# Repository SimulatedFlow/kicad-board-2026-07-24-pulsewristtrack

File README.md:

# 2026-07-24-pulsewristtrack

<!-- SF-STORE-BLOCK:BEGIN -->
## 🛒 Source-available — see before you buy

This repository contains the **full design files** of a commercial hardware board. It is **source-available, not open source**: read it, evaluate it, then buy a license to use it. See **LICENSE.md (source-available, purchase required)**.

**Get it / Buy:**
- **Order on eBay** (this board, bare PCB): https://www.ebay.de/itm/398223633551
- Product page (specs, photos, price): https://simulatedflow.teufel-engineering.com/platinen/2026-07-24-pulsewristtrack/
- eBay store — all our boards and PCB art: https://www.ebay.de/usr/simula-9
- Merch shop (dev & gaming): https://simulatedflow.myspreadshop.de
- Merch shop (Synthetica / EDM): https://synthetica.myspreadshop.de
- Direct / invoice (Simulated Flow UG): simulatedflow@gmail.com

### 📬 **Free Board Documentation & Firmware Pack**

Schematics, BOMs and example-firmware docs for our STM32 carrier boards. Get it by joining the newsletter — plus a heads-up when something new ships. Double opt-in, unsubscribe in one click, no address sharing.

👉 **[Get the free pack](https://simulatedflow.teufel-engineering.com/newsletter/hardware/?q=gh)**

_© 2026 Simulated Flow UG. All rights reserved._
<!-- SF-STORE-BLOCK:END -->

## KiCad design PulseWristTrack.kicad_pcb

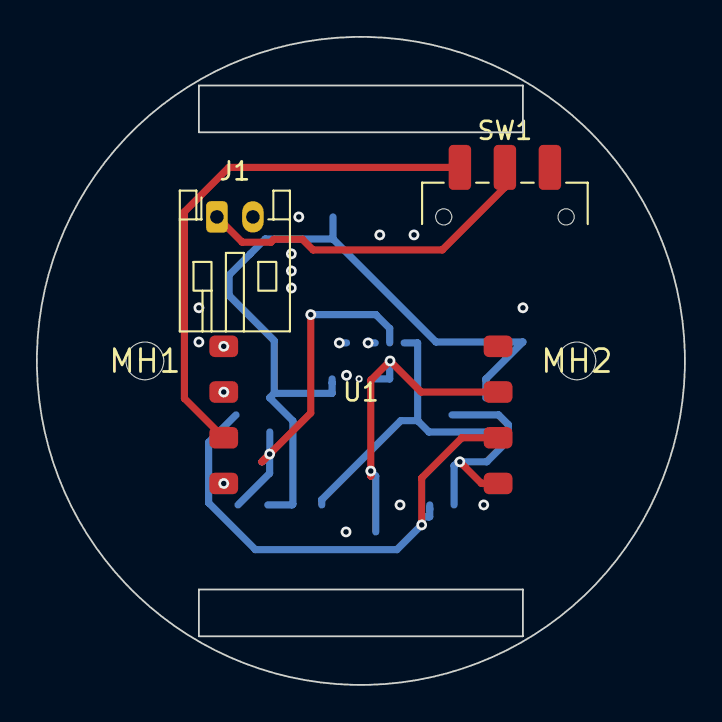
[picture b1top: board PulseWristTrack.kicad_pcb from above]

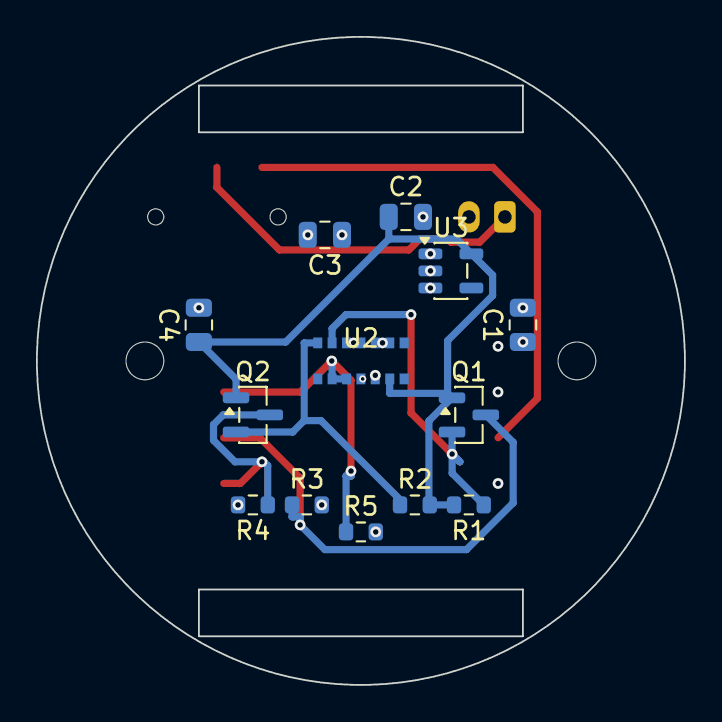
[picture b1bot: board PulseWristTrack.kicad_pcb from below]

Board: 4 copper layers, 36.0 x 36.0 mm, 18 parts (13 on the bottom side), 10 nets.

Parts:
C1, C3: 10uF; C_0805_2012Metric
C2, C4: 1uF; C_0805_2012Metric
J1: BATT_JST_PH; JST_PH_S2B-PH-K_1x02_P2.00mm_Horizontal
MH1, MH2: MountingHole_2.1mm
Q1, Q2: BSS138; SOT-23
R1, R2, R3, R4: 4.7k; R_0603_1608Metric
R5: 10k; R_0603_1608Metric
SW1: JS102011SAQN; SW_SPDT_CK_JS102011SAQN
U1: XIAO_nRF52840_Sense; XIAO_nRF52840
U2: MAX30102; MAX30102_OLGA14
U3: AP2112K-1.8; SOT-23-5

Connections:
+1V8: C2.1, C4.1, Q1.1, Q2.1, R1.2, R2.2, U2.9, U3.5
+3V3: C1.1, C3.1, R3.2, R4.2, R5.2, U1.3V3, U2.5, U2.6, U2.10, U3.1, U3.3
BAT+: J1.1, SW1.2
BAT_SW: SW1.1, U1.BAT+
GND: C1.2, C2.2, C3.2, C4.2, J1.2, U1.BAT-, U1.GND, U2.3, U2.4, U2.11, U3.2
INT: R5.1, U1.D3, U2.12, U2.13
SCL_1V8: Q2.2, R2.1, U2.1
SCL_3V3: Q2.3, R4.1, U1.D5
SDA_1V8: Q1.2, R1.1, U2.2
SDA_3V3: Q1.3, R3.1, U1.D4

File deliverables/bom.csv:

"Refs","Value","Footprint","Qty","DNP"
"C1","10uF","Capacitor_SMD:C_0805_2012Metric","1",""
"C2","1uF","Capacitor_SMD:C_0805_2012Metric","1",""
"C3","10uF","Capacitor_SMD:C_0805_2012Metric","1",""
"C4","1uF","Capacitor_SMD:C_0805_2012Metric","1",""
"J1","LiPo","Connector_JST:JST_PH_S2B-PH-K_1x02_P2.00mm_Horizontal","1",""
"Q1","BSS138","Package_TO_SOT_SMD:SOT-23","1",""
"Q2","BSS138","Package_TO_SOT_SMD:SOT-23","1",""
"R1","4.7k","Resistor_SMD:R_0603_1608Metric","1",""
"R2","4.7k","Resistor_SMD:R_0603_1608Metric","1",""
"R3","4.7k","Resistor_SMD:R_0603_1608Metric","1",""
"R4","4.7k","Resistor_SMD:R_0603_1608Metric","1",""
"R5","10k","Resistor_SMD:R_0603_1608Metric","1",""
"SW1","JS202011MQN","Button_Switch_SMD:SW_SPDT_PCM12","1",""
"U1","XIAO nRF52840 Sense","PulseWristTrack:XIAO_nRF52840","1",""
"U2","MAX30102","PulseWristTrack:MAX30102_OLGA14","1",""
"U3","AP2112K-1.8","Package_TO_SOT_SMD:SOT-23-5","1",""

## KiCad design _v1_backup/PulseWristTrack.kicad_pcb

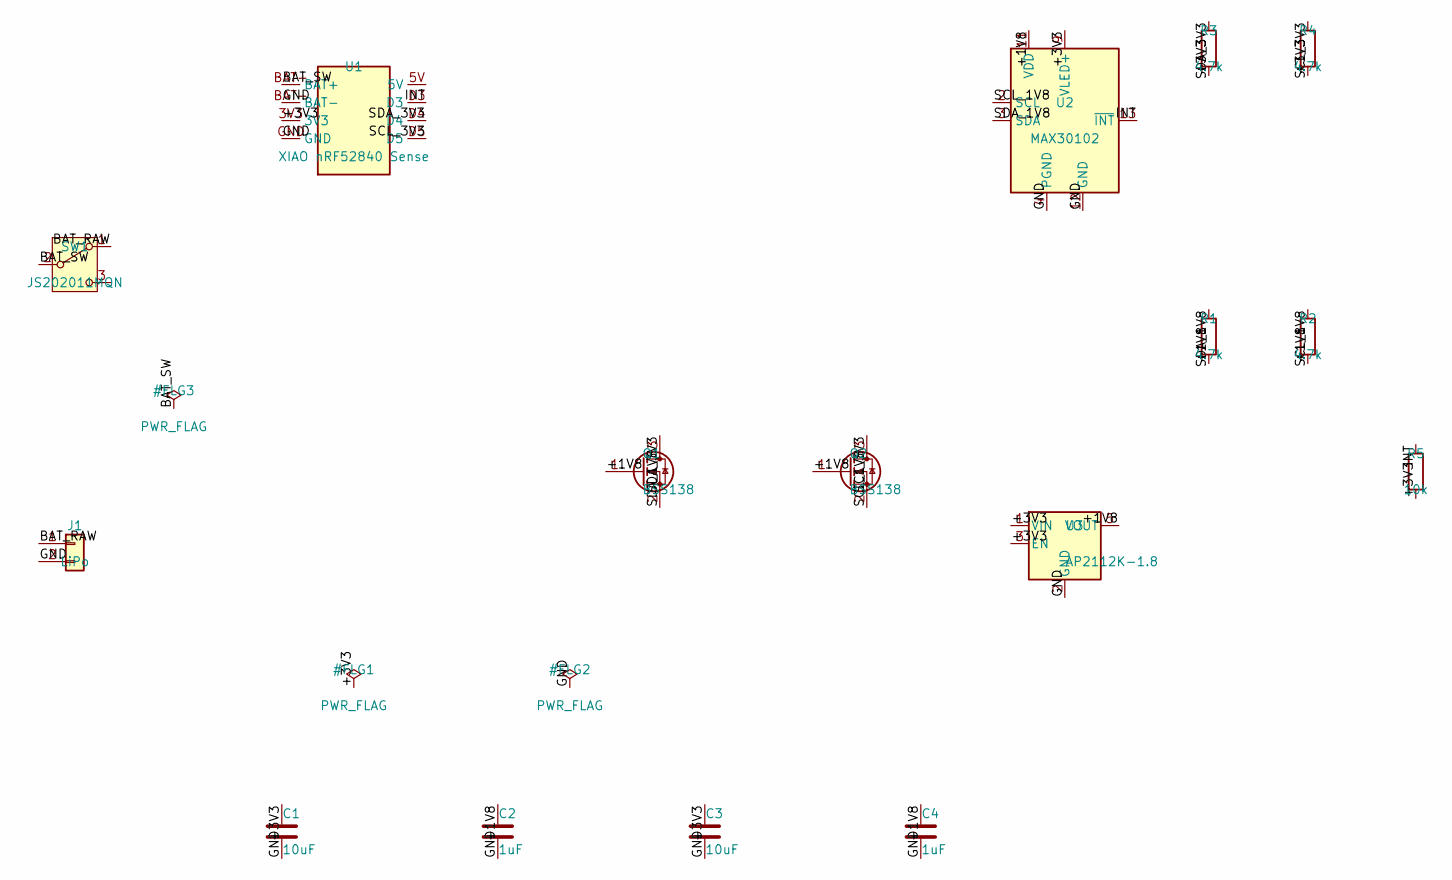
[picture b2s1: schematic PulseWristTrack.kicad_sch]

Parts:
C1, C3: 10uF; C_0805_2012Metric
C2, C4: 1uF; C_0805_2012Metric
J1: LiPo; JST_PH_S2B-PH-K_1x02_P2.00mm_Horizontal
Q1, Q2: BSS138; SOT-23
R1, R2, R3, R4: 4.7k; R_0603_1608Metric
R5: 10k; R_0603_1608Metric
SW1: JS202011MQN; SW_SPDT_PCM12
U1: XIAO nRF52840 Sense; XIAO_nRF52840
U2: MAX30102; MAX30102_OLGA14
U3: AP2112K-1.8; SOT-23-5

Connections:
+1V8: C2.1, C4.1, Q1.1 (G), Q2.1 (G), R1.2, R2.2, U2.11 (VDD), U3.5 (VOUT)
+3V3: C1.1, C3.1, R3.2, R4.2, R5.2, U1.3V3, U2.9 (VLED+), U2.10 (VLED+), U3.1 (VIN), U3.3 (EN)
BAT_RAW: J1.1, SW1.1 (A)
BAT_SW: SW1.2 (B), U1.BAT+
GND: C1.2, C2.2, C3.2, C4.2, J1.2, U1.BAT-, U1.GND, U2.4 (PGND), U2.12 (GND), U3.2 (GND)
INT: R5.1, U1.D3, U2.13 (~INT)
SCL_1V8: Q2.2 (S), R2.1, U2.2 (SCL)
SCL_3V3: Q2.3 (D), R4.1, U1.D5
SDA_1V8: Q1.2 (S), R1.1, U2.3 (SDA)
SDA_3V3: Q1.3 (D), R3.1, U1.D4

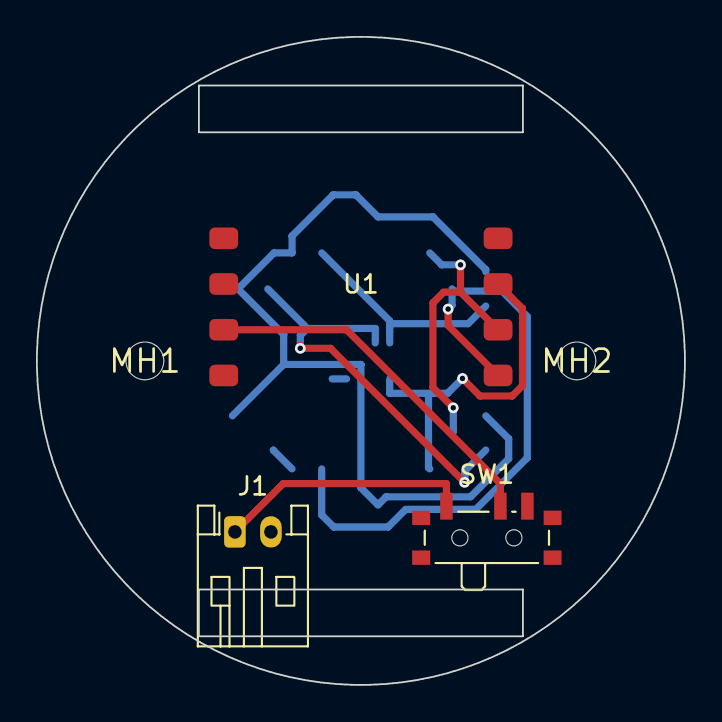
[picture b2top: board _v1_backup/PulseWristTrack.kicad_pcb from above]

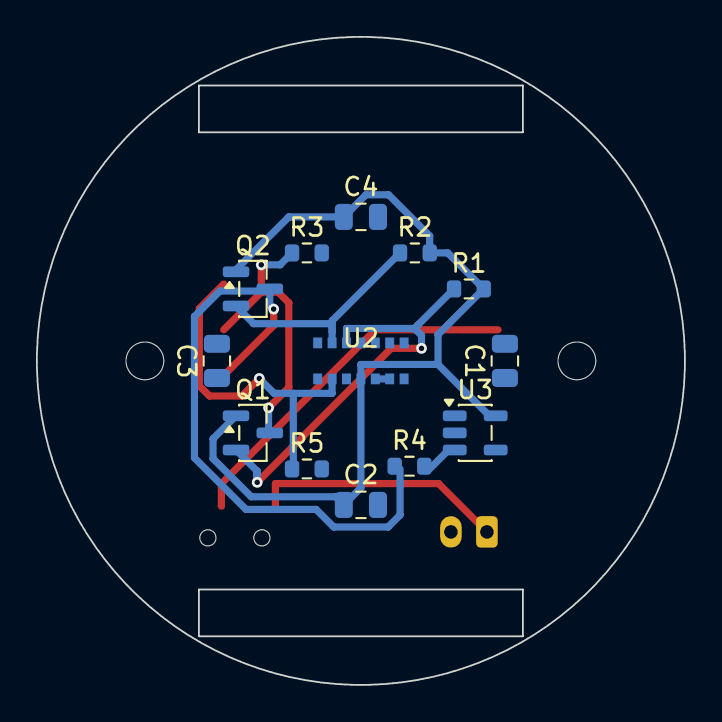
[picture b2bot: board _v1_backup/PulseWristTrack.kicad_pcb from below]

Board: 4 copper layers, 36.0 x 36.0 mm, 18 parts (13 on the bottom side), 10 nets.

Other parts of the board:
MH1, MH2: MountingHole_2.1mm
